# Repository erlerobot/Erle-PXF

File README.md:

Erle-PXF
===

Fork of the PXF board (http://github.com/diydrones/PXF) made by Erle Robotics.

This project is for developers, it will NOT be supported by the DIYDrones or Ardupilot suppoert forums for general users. This means we do not expect that this board will be plug and play, nor do we intend it to be.

Credit to Philip Rowse and Erle Robotics.

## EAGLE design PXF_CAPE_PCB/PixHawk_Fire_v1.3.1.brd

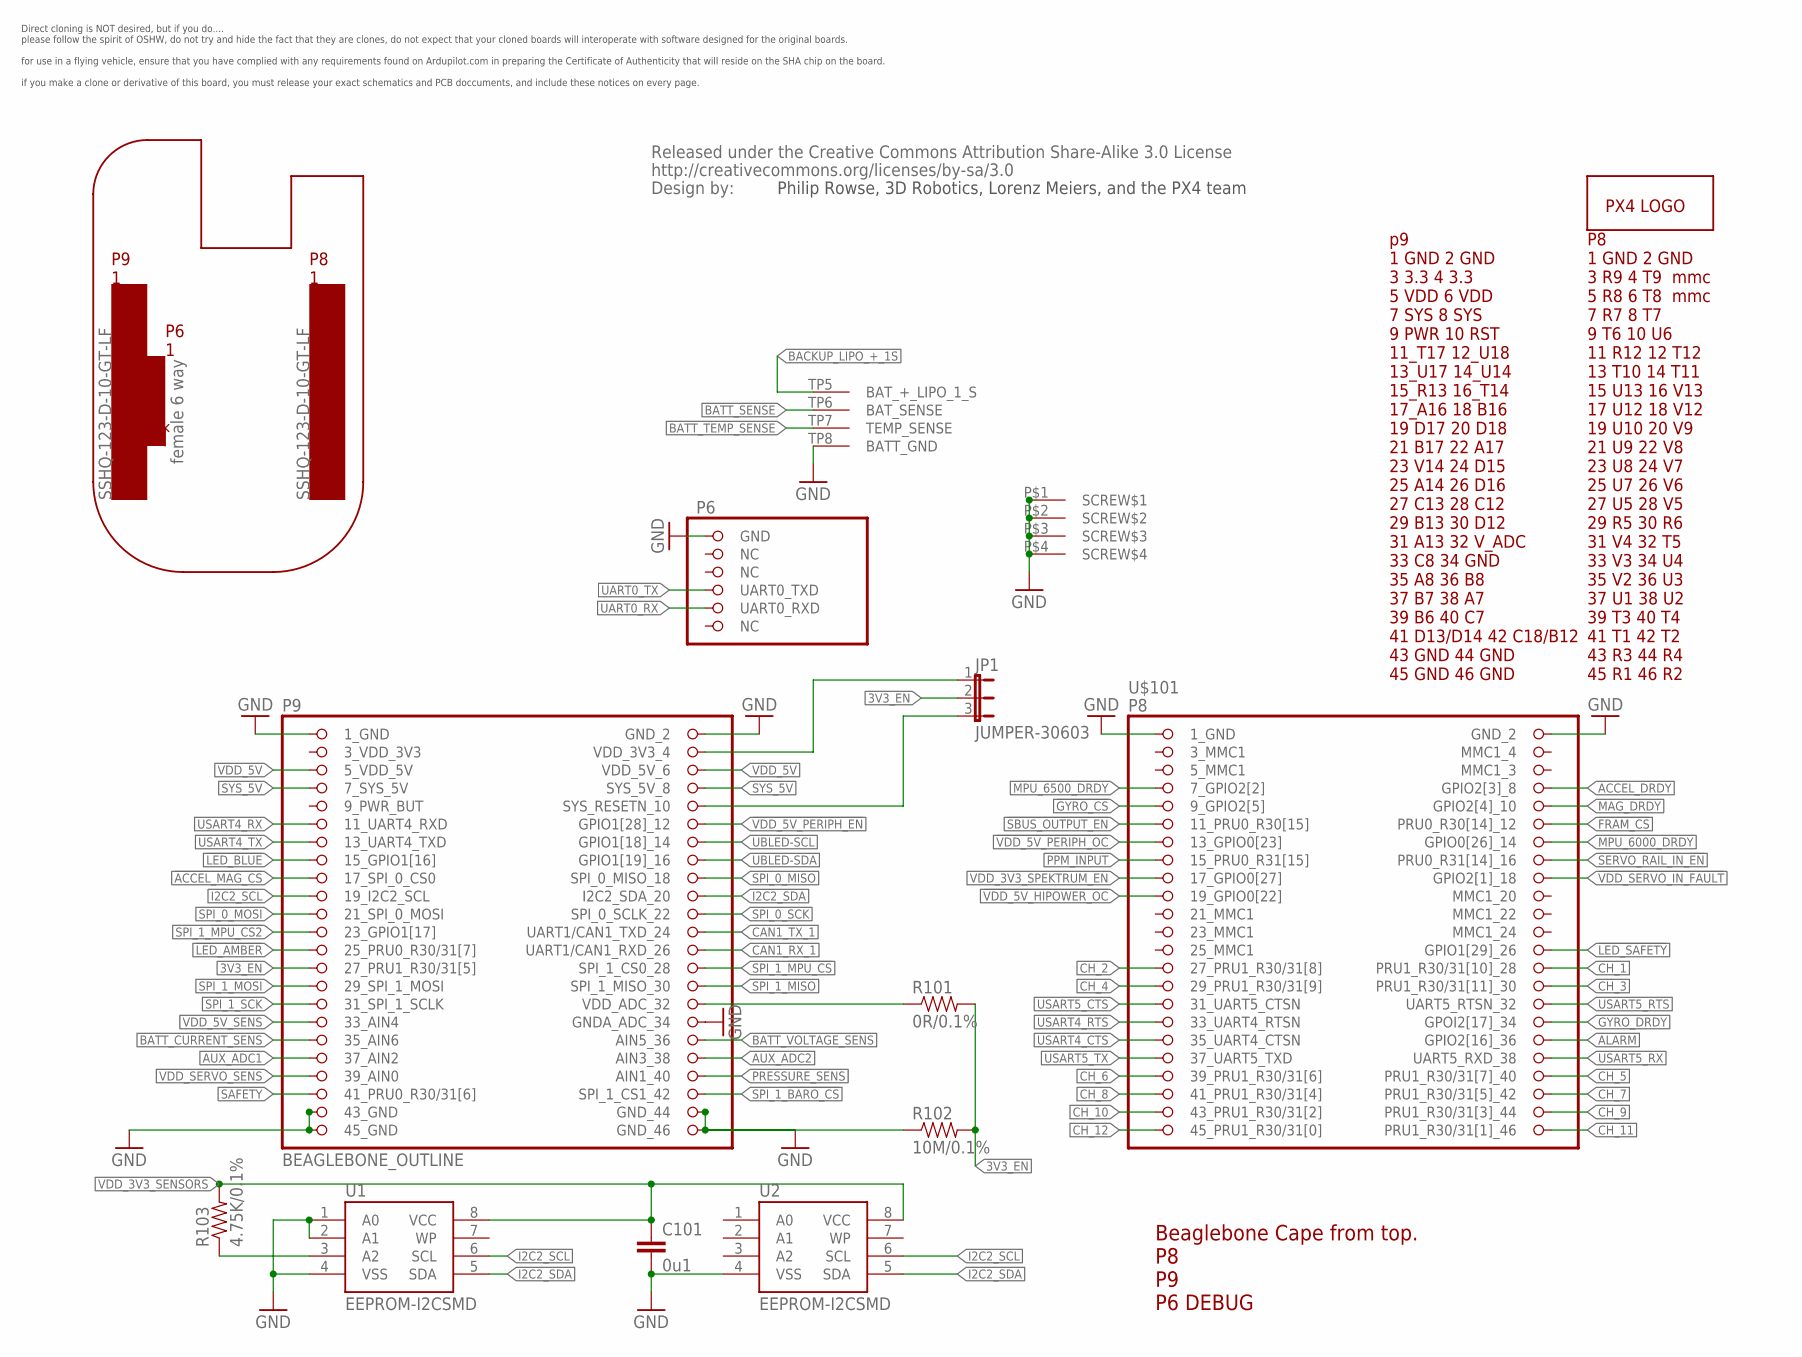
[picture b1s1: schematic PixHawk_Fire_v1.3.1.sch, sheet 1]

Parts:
C101: 0u1; 0402-CAP; PARTNO CC0402ZRY5V7BB104
JP1: JUMPER-30603; SJ_3_0603_PASTE1&2; PARTNO RC0603JR-070RL
R101: 0R/0.1%; 0402-RES; PARTNO RC0402FR-070RL
R102: 10M/0.1%; 0402-RES; PARTNO RC0402FR-0710ML
R103: 4.75K/0.1%; 0402-RES; PARTNO RC0402FR-074K75L
U1: EEPROM-I2CSMD; SO08; PARTNO AT24CS32-SSHM
U2: EEPROM-I2CSMD; SO08; PARTNO ATSHA204-SH-DA-TTR-ND
U$1: PX4-LOGO; PIXHAWK-FIRE-LOGO-30
U$6: CREATIVE_COMMONS
U$101: BEAGLEBONE_OUTLINE; BEAGLEBONE_SHIELD

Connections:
3V3_EN: JP1.2, R101.P$2 (2), R102.P$2 (2), U$101.73 (27_PRU1_R30/31[5]); also elsewhere on the board
3_VDD_3V3: U$101.49 (3_VDD_3V3)
!ACCEL_MAG_CS: U$101.63 (17_SPI_0_CS0); also elsewhere on the board
!FRAM_CS: U$101.12 (PRU0_R30[14]_12); also elsewhere on the board
!GYRO_CS: U$101.9 (9_GPIO2[5]); also elsewhere on the board
!LED_AMBER: U$101.71 (25_PRU0_R30/31[7]); also elsewhere on the board
!LED_BLUE: U$101.61 (15_GPIO1[16]); also elsewhere on the board
!LED_SAFETY: U$101.26 (GPIO1[29]_26); also elsewhere on the board
!SBUS_OUTPUT_EN: U$101.11 (11_PRU0_R30[15]); also elsewhere on the board
!VDD_5V_HIPOWER_OC: U$101.19 (19_GPIO0[22]); also elsewhere on the board
!VDD_5V_PERIPH_EN: U$101.58 (GPIO1[28]_12); also elsewhere on the board
!VDD_5V_PERIPH_OC: U$101.13 (13_GPIO0[23]); also elsewhere on the board
!VDD_SERVO_IN_FAULT: U$101.18 (GPIO2[1]_18); also elsewhere on the board
ACCEL_DRDY: U$101.8 (GPIO2[3]_8); also elsewhere on the board
ALARM: U$101.36 (GPIO2[16]_36); also elsewhere on the board
AUX_ADC1: U$101.83 (37_AIN2); also elsewhere on the board
AUX_ADC2: U$101.84 (AIN3_38); also elsewhere on the board
BACKUP_LIPO_+_1S: U$101.TP5 (BAT_+_LIPO_1_S); also elsewhere on the board
BATT_CURRENT_SENS: U$101.81 (35_AIN6); also elsewhere on the board
BATT_SENSE: U$101.TP6 (BAT_SENSE); also elsewhere on the board
BATT_TEMP_SENSE: U$101.TP7 (TEMP_SENSE); also elsewhere on the board
BATT_VOLTAGE_SENS: U$101.82 (AIN5_36); also elsewhere on the board
CH_1: U$101.28 (PRU1_R30/31[10]_28); also elsewhere on the board
CH_2: U$101.27 (27_PRU1_R30/31[8]); also elsewhere on the board
CH_3: U$101.30 (PRU1_R30/31[11]_30); also elsewhere on the board
CH_4: U$101.29 (29_PRU1_R30/31[9]); also elsewhere on the board
CH_5: U$101.40 (PRU1_R30/31[7]_40); also elsewhere on the board
CH_6: U$101.39 (39_PRU1_R30/31[6]); also elsewhere on the board
CH_7: U$101.42 (PRU1_R30/31[5]_42); also elsewhere on the board
CH_8: U$101.41 (41_PRU1_R30/31[4]); also elsewhere on the board
CH_9: U$101.44 (PRU1_R30/31[3]_44); also elsewhere on the board
CH_10: U$101.43 (43_PRU1_R30/31[2]); also elsewhere on the board
CH_11: U$101.46 (PRU1_R30/31[1]_46); also elsewhere on the board
CH_12: U$101.45 (45_PRU1_R30/31[0]); also elsewhere on the board
GND: C101.P$2 (2), R102.P$1 (1), U1.1 (A0), U1.2 (A1), U1.4 (VSS), U2.4 (VSS), U$101.1 (1_GND), U$101.2 (GND_2), U$101.47 (1_GND), U$101.48 (GND_2), U$101.80 (GNDA_ADC_34), U$101.89 (43_GND), U$101.90 (GND_44), U$101.91 (45_GND), U$101.92 (GND_46), U$101.93 (GND), U$101.P$1 (SCREW$1), U$101.P$2 (SCREW$2), U$101.P$3 (SCREW$3), U$101.P$4 (SCREW$4), U$101.TP8 (BATT_GND); also elsewhere on the board
GYRO_DRDY: U$101.34 (GPOI2[17]_34); also elsewhere on the board
I2C2_SCL: U1.6 (SCL), U2.6 (SCL), U$101.65 (19_I2C2_SCL); also elsewhere on the board
I2C2_SDA: U1.5 (SDA), U2.5 (SDA), U$101.66 (I2C2_SDA_20); also elsewhere on the board
MAG_DRDY: U$101.10 (GPIO2[4]_10); also elsewhere on the board
MPU_6000_DRDY: U$101.14 (GPIO0[26]_14); also elsewhere on the board
MPU_6500_DRDY: U$101.7 (7_GPIO2[2]); also elsewhere on the board
unnamed: R103.P$1 (1), U1.3 (A2)
unnamed: JP1.1, U$101.50 (VDD_3V3_4)
unnamed: JP1.3, U$101.56 (SYS_RESETN_10)
PPM_INPUT: U$101.15 (15_PRU0_R31[15]); also elsewhere on the board
PRESSURE_SENS: U$101.86 (AIN1_40); also elsewhere on the board
SAFETY: U$101.87 (41_PRU0_R30/31[6]); also elsewhere on the board
SERVO_RAIL_IN_!EN: U$101.16 (PRU0_R31[14]_16); also elsewhere on the board
SPI_0_MISO: U$101.64 (SPI_0_MISO_18); also elsewhere on the board
SPI_0_MOSI: U$101.67 (21_SPI_0_MOSI); also elsewhere on the board
SPI_0_SCK: U$101.68 (SPI_0_SCLK_22); also elsewhere on the board
SPI_1_!BARO_CS: U$101.88 (SPI_1_CS1_42); also elsewhere on the board
SPI_1_!MPU_CS: U$101.74 (SPI_1_CS0_28); also elsewhere on the board
SPI_1_!MPU_CS2: U$101.69 (23_GPIO1[17]); also elsewhere on the board
SPI_1_MISO: U$101.76 (SPI_1_MISO_30); also elsewhere on the board
SPI_1_MOSI: U$101.75 (29_SPI_1_MOSI); also elsewhere on the board
SPI_1_SCK: U$101.77 (31_SPI_1_SCLK); also elsewhere on the board
SYS_5V: U$101.53 (7_SYS_5V), U$101.54 (SYS_5V_8); also elsewhere on the board
UART0_RX: U$101.97 (UART0_RXD); also elsewhere on the board
UART0_TX: U$101.96 (UART0_TXD); also elsewhere on the board
UBLED-SCL: U$101.60 (GPIO1[18]_14); also elsewhere on the board
UBLED-SDA: U$101.62 (GPIO1[19]_16); also elsewhere on the board
USART4_CTS: U$101.35 (35_UART4_CTSN); also elsewhere on the board
USART4_RTS: U$101.33 (33_UART4_RTSN); also elsewhere on the board
USART4_RX: U$101.57 (11_UART4_RXD); also elsewhere on the board
USART4_TX: U$101.59 (13_UART4_TXD); also elsewhere on the board
USART5_CTS: U$101.31 (31_UART5_CTSN); also elsewhere on the board
USART5_RTS: U$101.32 (UART5_RTSN_32); also elsewhere on the board
USART5_RX: U$101.38 (UART5_RXD_38); also elsewhere on the board
USART5_TX: U$101.37 (37_UART5_TXD); also elsewhere on the board
VDD_3V3_SENSORS: C101.P$1 (1), R103.P$2 (2), U1.8 (VCC), U2.8 (VCC); also elsewhere on the board
VDD_3V3_SPEKTRUM_EN: U$101.17 (17_GPIO0[27]); also elsewhere on the board
VDD_5V: U$101.51 (5_VDD_5V), U$101.52 (VDD_5V_6); also elsewhere on the board
VDD_5V_SENS: U$101.79 (33_AIN4); also elsewhere on the board
VDD_ADC: R101.P$1 (1), U$101.78 (VDD_ADC_32)
VDD_SERVO_SENS: U$101.85 (39_AIN0); also elsewhere on the board

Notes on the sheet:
Beaglebone Cape from top. P8 P9 P6 DEBUG
Philip Rowse, 3D Robotics, Lorenz Meiers, and the PX4 team
Direct cloning is NOT desired, but if you do.... please follow the spirit of OSHW, do not try and hide the fact that they are clones, do not expect that your cloned boards will interoperate with software designed for the original boards. for use in a flying vehicle, ensure that you have complied wi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

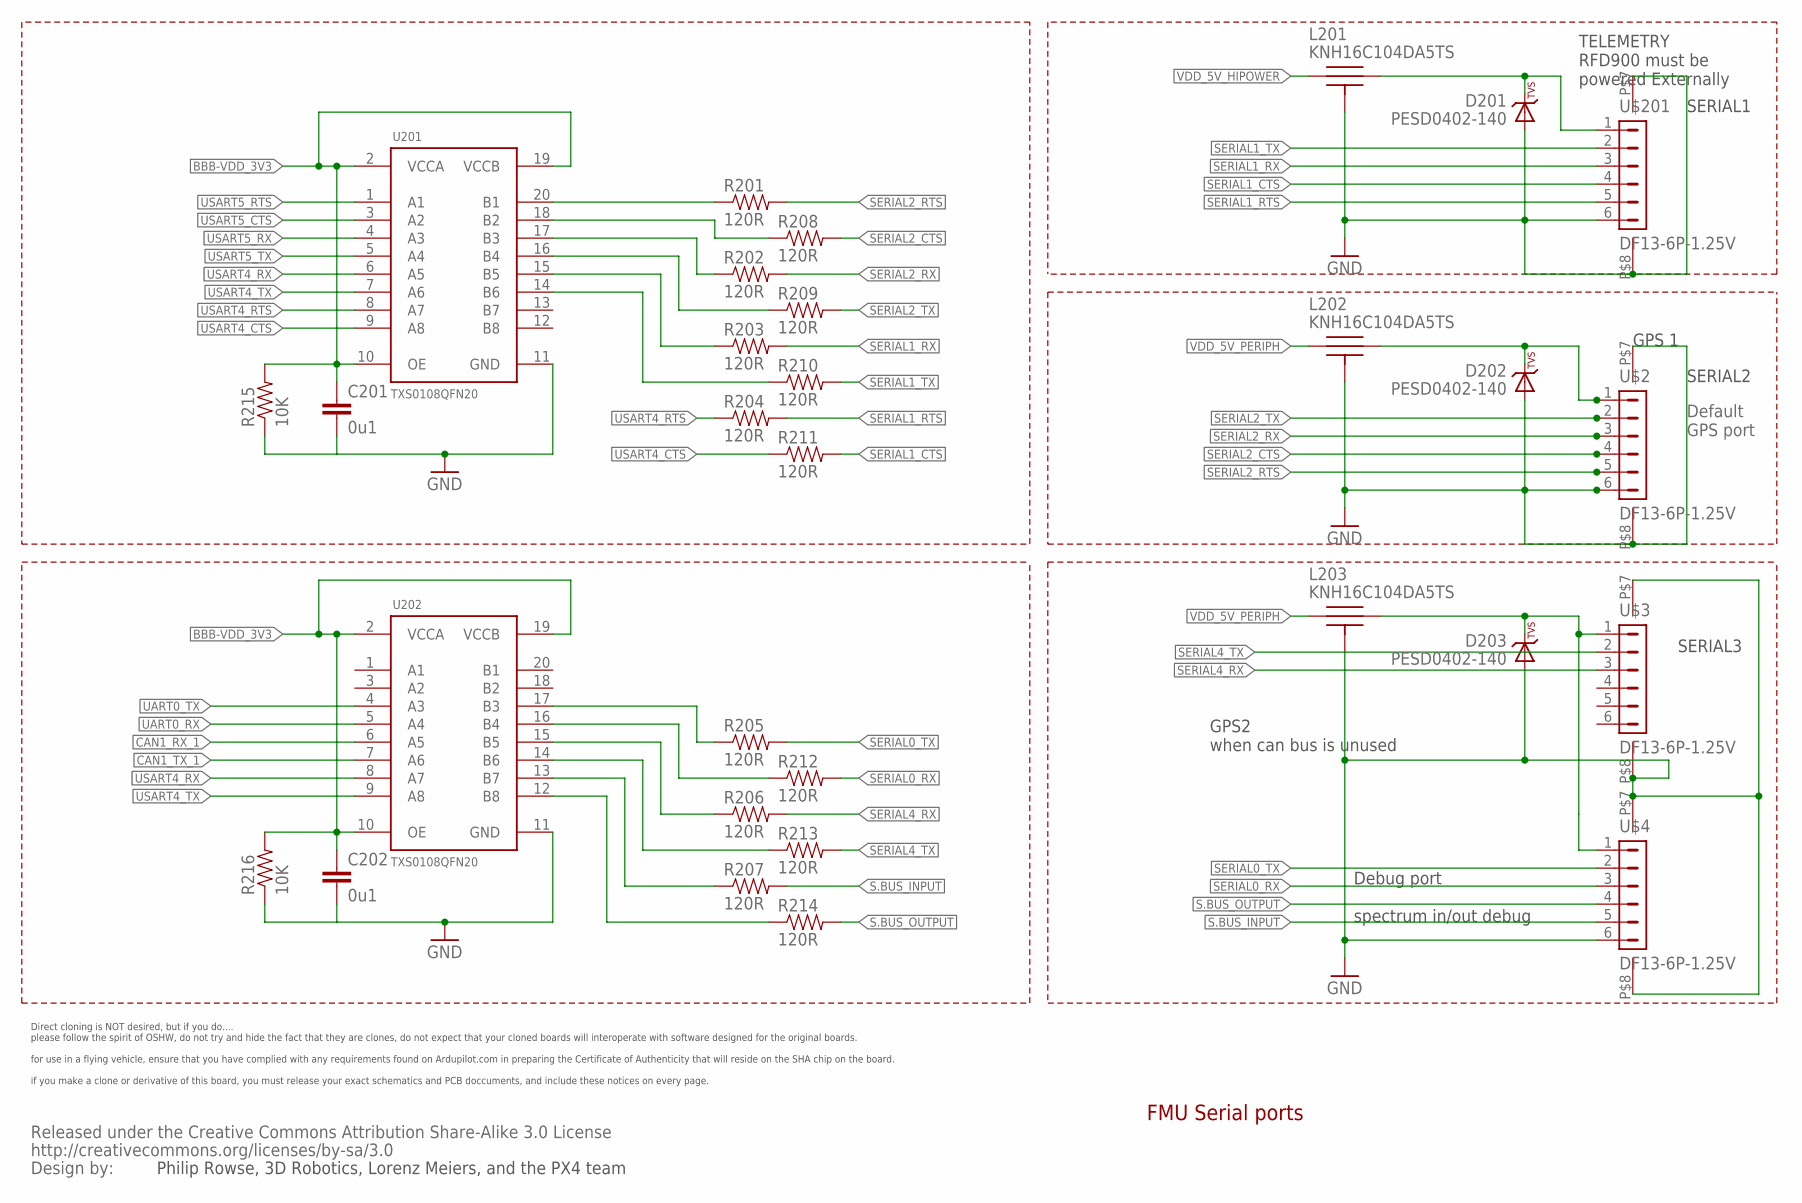
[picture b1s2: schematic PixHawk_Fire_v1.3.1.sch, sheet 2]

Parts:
C201, C202: 0u1; 0402-CAP; PARTNO CC0402ZRY5V7BB104
D201, D202, D203: PESD0402-140; 0402-TVS; PARTNO PESD0402-140
L201, L202, L203: KNH16C104DA5TS; KYOCERA-KNH16-DA; PARTNO KNH16C104DA5TS
R201, R202, R203, R204, R205, R206, R207, R208, R209, R210, R211, R212, R213, R214: 120R; 0402-RES; PARTNO RC0402FR-07120RL
R215, R216: 10K; 0402-RES; PARTNO ERA-2AEB103X
U201, U202: TXS0108QFN20; QFN20-RGY; PARTNO TXS0108ERGYR
U$2, U$3, U$4, U$201: DF13-6P-1.25V; DF13C-6P-1.25V; PARTNO DF13C-6P-1.25V(20)
U$5: CREATIVE_COMMONS

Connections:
BBB-VDD_3V3: C201.P$1 (1), C202.P$1 (1), R215.P$2 (2), R216.P$2 (2), U201.2 (VCCA), U201.10 (OE), U201.19 (VCCB), U202.2 (VCCA), U202.10 (OE), U202.19 (VCCB); also elsewhere on the board
CAN1_RX_1: U202.6 (A5); also elsewhere on the board
CAN1_TX_1: U202.7 (A6); also elsewhere on the board
GND: C201.P$2 (2), C202.P$2 (2), D201.A, D202.A, D203.A, L201.P$3, L201.P$4, L201.P$5, L202.P$3, L202.P$4, L202.P$5, L203.P$3, L203.P$4, L203.P$5, R215.P$1 (1), R216.P$1 (1), U201.11 (GND), U202.11 (GND), U$2.6, U$2.P$7, U$2.P$8, U$3.P$7, U$3.P$8, U$4.6, U$4.P$7, U$4.P$8, U$201.6, U$201.P$7, U$201.P$8; also elsewhere on the board
unnamed: D201.C, L201.P$2, U$201.1
unnamed: R205.P$1 (1), U202.17 (B3)
unnamed: R212.P$1 (1), U202.16 (B4)
unnamed: R208.P$1 (1), U201.18 (B2)
unnamed: R201.P$1 (1), U201.20 (B1)
unnamed: R202.P$1 (1), U201.17 (B3)
unnamed: R209.P$1 (1), U201.16 (B4)
unnamed: R203.P$1 (1), U201.15 (B5)
unnamed: R210.P$1 (1), U201.14 (B6)
unnamed: R207.P$1 (1), U202.13 (B7)
unnamed: R214.P$1 (1), U202.12 (B8)
unnamed: R206.P$1 (1), U202.15 (B5)
unnamed: R213.P$1 (1), U202.14 (B6)
unnamed: D203.C, L203.P$2, U$3.1, U$4.1
unnamed: D202.C, L202.P$2, U$2.1
S.BUS_INPUT: R207.P$2 (2), U$4.5; also elsewhere on the board
S.BUS_OUTPUT: R214.P$2 (2), U$4.4; also elsewhere on the board
SERIAL0_RX: R212.P$2 (2), U$4.3
SERIAL0_TX: R205.P$2 (2), U$4.2
SERIAL1_CTS: R211.P$2 (2), U$201.4
SERIAL1_RTS: R204.P$2 (2), U$201.5
SERIAL1_RX: R203.P$2 (2), U$201.3; also elsewhere on the board
SERIAL1_TX: R210.P$2 (2), U$201.2; also elsewhere on the board
SERIAL2_CTS: R208.P$2 (2), U$2.4
SERIAL2_RTS: R201.P$2 (2), U$2.5
SERIAL2_RX: R202.P$2 (2), U$2.3; also elsewhere on the board
SERIAL2_TX: R209.P$2 (2), U$2.2; also elsewhere on the board
SERIAL4_RX: R206.P$2 (2), U$3.3; also elsewhere on the board
SERIAL4_TX: R213.P$2 (2), U$3.2; also elsewhere on the board
UART0_RX: U202.5 (A4); also elsewhere on the board
UART0_TX: U202.4 (A3); also elsewhere on the board
USART4_CTS: R211.P$1 (1), U201.9 (A8); also elsewhere on the board
USART4_RTS: R204.P$1 (1), U201.8 (A7); also elsewhere on the board
USART4_RX: U201.6 (A5), U202.8 (A7); also elsewhere on the board
USART4_TX: U201.7 (A6), U202.9 (A8); also elsewhere on the board
USART5_CTS: U201.3 (A2); also elsewhere on the board
USART5_RTS: U201.1 (A1); also elsewhere on the board
USART5_RX: U201.4 (A3); also elsewhere on the board
USART5_TX: U201.5 (A4); also elsewhere on the board
VDD_5V_HIPOWER: L201.P$1; also elsewhere on the board
VDD_5V_PERIPH: L202.P$1, L203.P$1; also elsewhere on the board

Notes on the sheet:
FMU Serial ports
SERIAL2
SERIAL1
SERIAL3
Default GPS port
TELEMETRY RFD900 must be powered Externally
GPS 1
Debug port spectrum in/out debug
GPS2 when can bus is unused
Philip Rowse, 3D Robotics, Lorenz Meiers, and the PX4 team
Direct cloning is NOT desired, but if you do.... please follow the spirit of OSHW, do not try and hide the fact that they are clones, do not expect that your cloned boards will interoperate with software designed for the original boards. for use in a flying vehicle, ensure that you have complied wi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

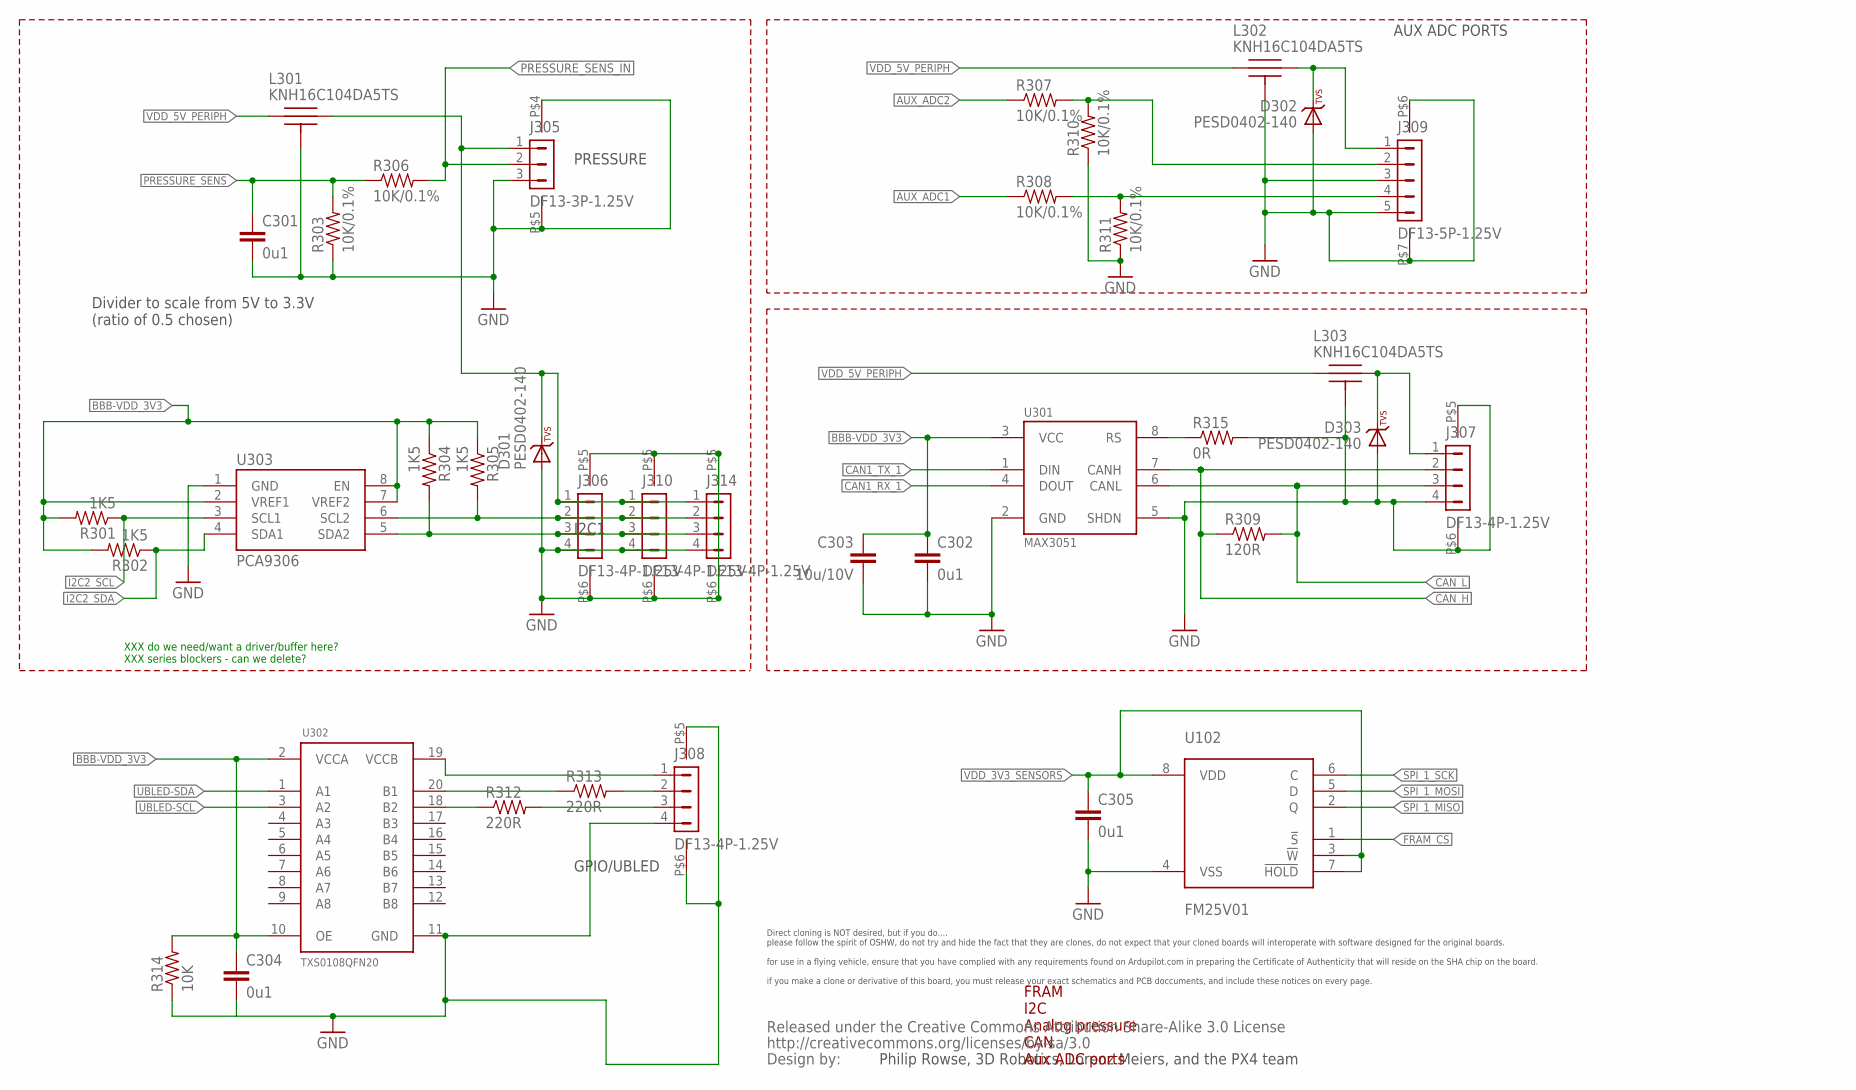
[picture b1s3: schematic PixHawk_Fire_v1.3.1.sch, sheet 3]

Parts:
C301, C302, C304, C305: 0u1; 0402-CAP; PARTNO CC0402ZRY5V7BB104
C303: 10u/10V; 0805-CAP; PARTNO CC0805ZKY5V6BB106
D301, D302, D303: PESD0402-140; 0402-TVS; PARTNO PESD0402-140
J305: DF13-3P-1.25V; DF13C-3P-1.25V; PARTNO DF13C-3P-1.25V(20)
J306, J307, J308, J310, J314: DF13-4P-1.25V; DF13C-4P-1.25V; PARTNO DF13C-4P-1.25V(20)
J309: DF13-5P-1.25V; DF13C-5P-1.25V; PARTNO DF13C-5P-1.25V(20)
L301, L302, L303: KNH16C104DA5TS; KYOCERA-KNH16-DA; PARTNO KNH16C104DA5TS
R301, R302, R304, R305: 1K5; 0402-RES; PARTNO RC0402FR-071K5L
R303, R306, R307, R308, R310, R311: 10K/0.1%; 0402-RES; PARTNO ERA-2AEB103X
R309: 120R; 0402-RES; PARTNO RC0402FR-07120RL
R312, R313: 220R; 0402-RES; PARTNO RC0402FR-07220RL
R314: 10K; 0402-RES; PARTNO ERA-2AEB103X
R315: 0R; 0402-RES; PARTNO RC0402FR-070RL
U102: FM25V01; SO08; PARTNO FM25V01-G
U301: MAX3051; SOT23-8; PARTNO MAX3051EKA
U302: TXS0108QFN20; QFN20-RGY; PARTNO TXS0108ERGYR
U303: PCA9306; PARTNO PCA9306DQER
U$7: CREATIVE_COMMONS

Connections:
!FRAM_CS: U102.1 (!S); also elsewhere on the board
AUX_ADC1: R308.P$1 (1); also elsewhere on the board
AUX_ADC2: R307.P$1 (1); also elsewhere on the board
BBB-VDD_3V3: C302.P$1 (1), C303.P$1 (1), C304.P$1 (1), R301.P$2 (2), R302.P$2 (2), R304.P$1 (1), R305.P$1 (1), R314.P$2 (2), U301.3 (VCC), U302.2 (VCCA), U302.10 (OE), U303.2 (VREF1), U303.7 (VREF2), U303.8 (EN); also elsewhere on the board
CAN1_RX_1: U301.4 (DOUT); also elsewhere on the board
CAN1_TX_1: U301.1 (DIN); also elsewhere on the board
CAN_H: J307.2, R309.P$1 (1), U301.7 (CANH); also elsewhere on the board
CAN_L: J307.3, R309.P$2 (2), U301.6 (CANL); also elsewhere on the board
FMU_AUX_ADC1_PROT: J309.4, R308.P$2 (2), R311.P$2 (2)
FMU_AUX_ADC2_PROT: J309.2, R307.P$2 (2), R310.P$2 (2)
GND: C301.P$2 (2), C302.P$2 (2), C303.P$2 (2), C304.P$2 (2), C305.P$2 (2), D301.A, D302.A, D303.A, J305.3, J305.P$4, J305.P$5, J306.4, J306.P$5, J306.P$6, J307.4, J307.P$5, J307.P$6, J308.4, J308.P$5, J308.P$6, J309.3, J309.5, J309.P$6, J309.P$7, J310.4, J310.P$5, J310.P$6, J314.4, J314.P$5, J314.P$6, L301.P$3, L301.P$4, L301.P$5, L302.P$3, L302.P$4, L302.P$5, L303.P$3, L303.P$4, L303.P$5, R303.P$1 (1), R310.P$1 (1), R311.P$1 (1), R314.P$1 (1), R315.P$2 (2), U102.4 (VSS), U301.2 (GND), U301.5 (SHDN), U302.11 (GND), U303.1 (GND); also elsewhere on the board
I2C2_SCL: R301.P$1 (1), U303.3 (SCL1); also elsewhere on the board
I2C2_SDA: R302.P$1 (1), U303.4 (SDA1); also elsewhere on the board
unnamed: R313.P$1 (1), U302.20 (B1)
unnamed: J306.2, J310.2, J314.2, R305.P$2 (2), U303.6 (SCL2)
unnamed: J306.3, J310.3, J314.3, R304.P$2 (2), U303.5 (SDA2)
unnamed: R312.P$1 (1), U302.18 (B2)
unnamed: D301.C, J305.1, J306.1, J310.1, J314.1, L301.P$2
unnamed: J308.3, R312.P$2 (2)
unnamed: J308.2, R313.P$2 (2)
unnamed: J308.1, U302.19 (VCCB)
unnamed: D303.C, J307.1, L303.P$2
unnamed: R315.P$1 (1), U301.8 (RS)
unnamed: D302.C, J309.1, L302.P$2
PRESSURE_SENS: C301.P$1 (1), R303.P$2 (2), R306.P$1 (1); also elsewhere on the board
PRESSURE_SENS_IN: J305.2, R306.P$2 (2); also elsewhere on the board
SPI_1_MISO: U102.2 (Q); also elsewhere on the board
SPI_1_MOSI: U102.5 (D); also elsewhere on the board
SPI_1_SCK: U102.6 (C); also elsewhere on the board
UBLED-SCL: U302.3 (A2); also elsewhere on the board
UBLED-SDA: U302.1 (A1); also elsewhere on the board
VDD_3V3_SENSORS: C305.P$1 (1), U102.3 (!W), U102.7 (!HOLD), U102.8 (VDD); also elsewhere on the board
VDD_5V_PERIPH: L301.P$1, L302.P$1, L303.P$1; also elsewhere on the board

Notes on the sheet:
PRESSURE
XXX do we need/want a driver/buffer here? XXX series blockers - can we delete?
I2C1
AUX ADC PORTS
FRAM I2C Analog pressure CAN Aux ADC ports
Divider to scale from 5V to 3.3V (ratio of 0.5 chosen)
GPIO/UBLED
Philip Rowse, 3D Robotics, Lorenz Meiers, and the PX4 team
Direct cloning is NOT desired, but if you do.... please follow the spirit of OSHW, do not try and hide the fact that they are clones, do not expect that your cloned boards will interoperate with software designed for the original boards. for use in a flying vehicle, ensure that you have complied wi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

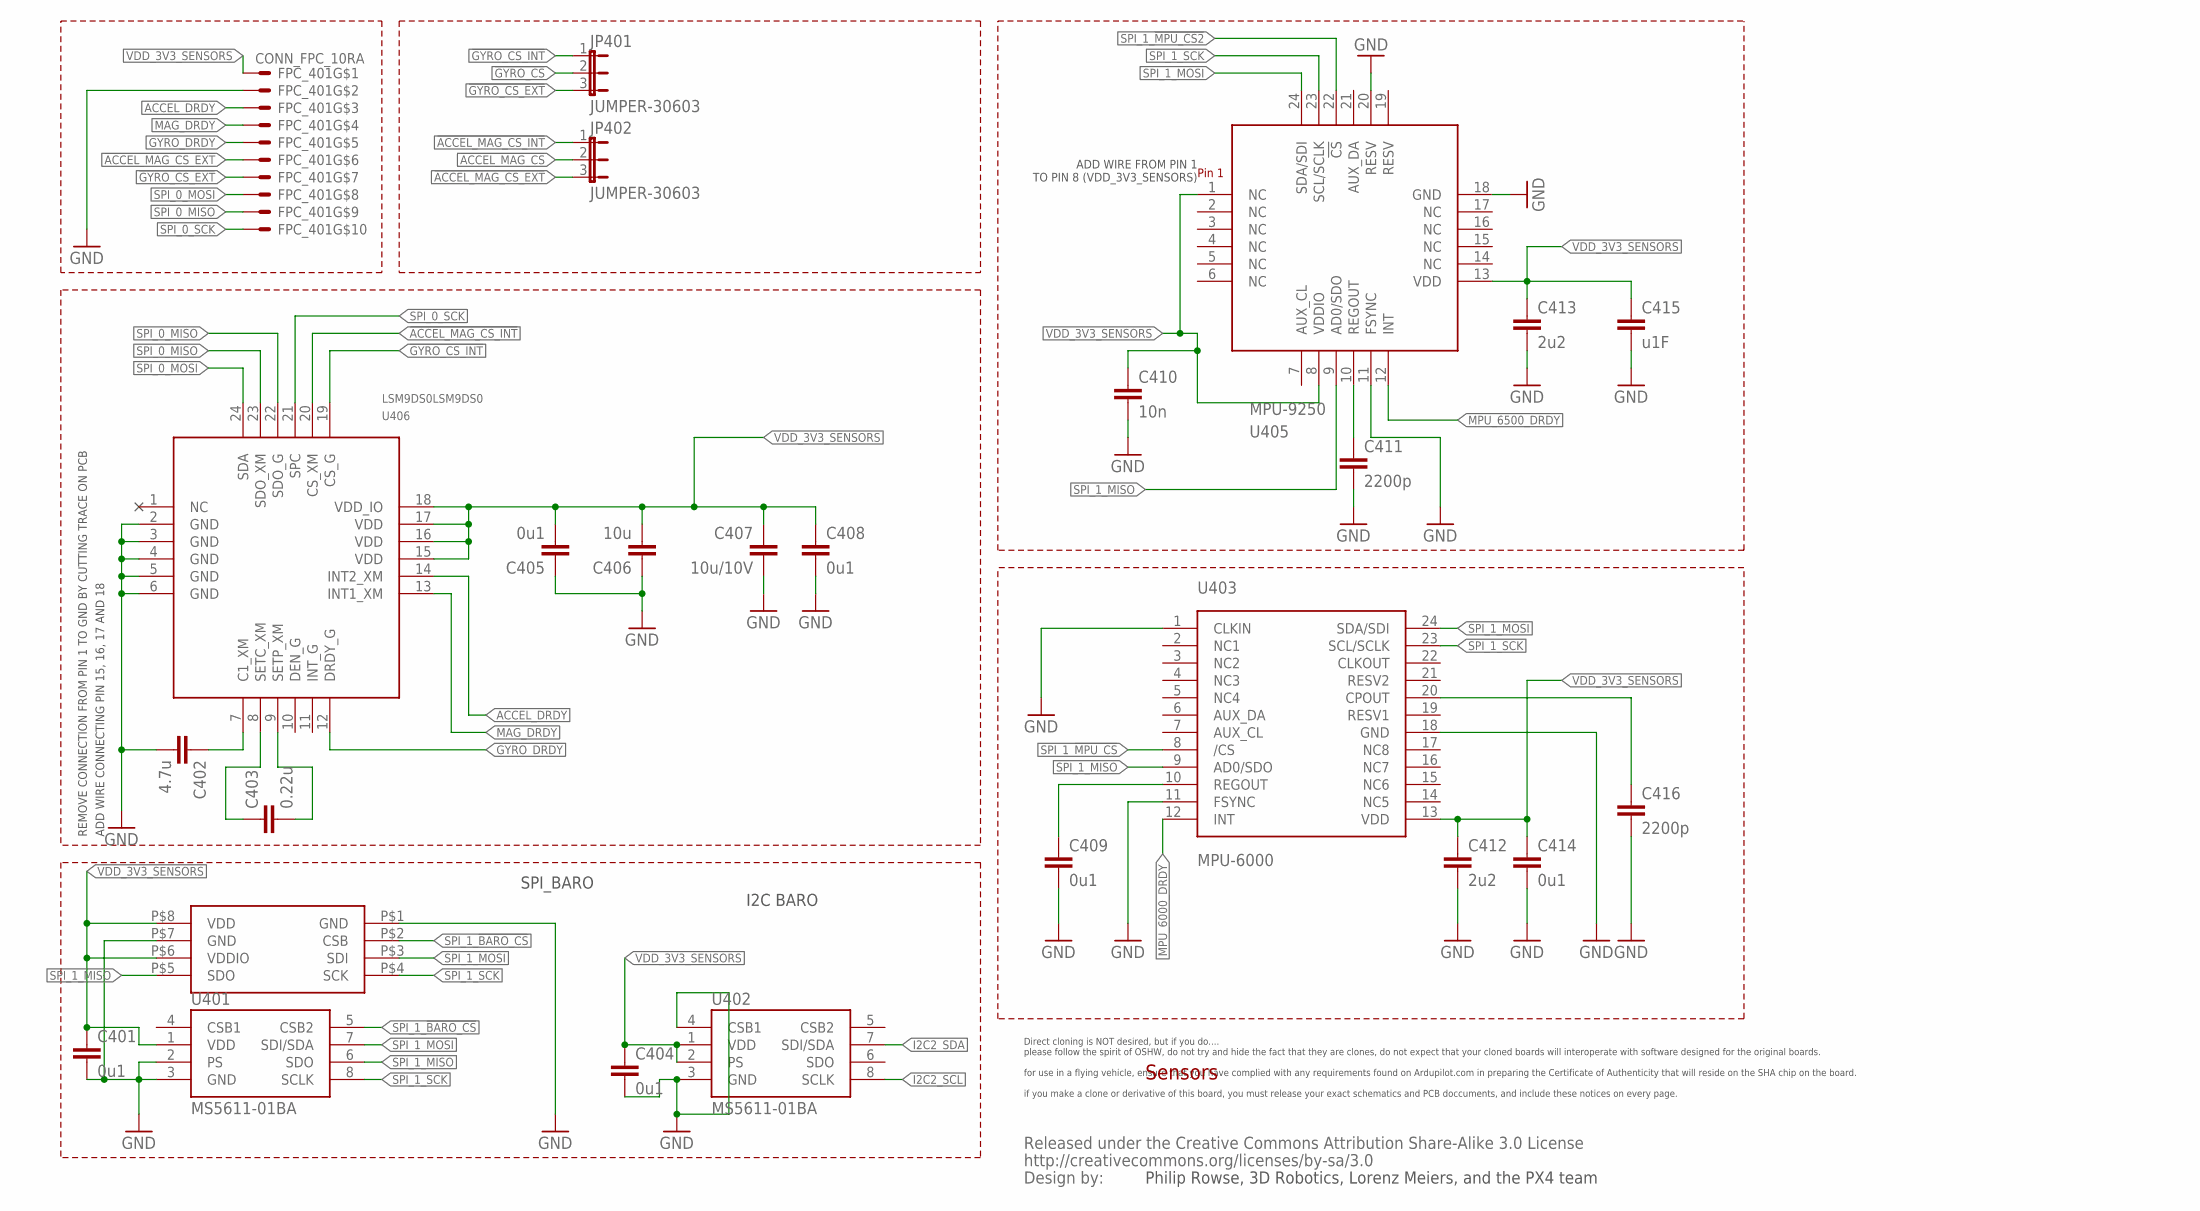
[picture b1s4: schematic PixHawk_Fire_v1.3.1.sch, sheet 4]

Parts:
C401, C404, C408: 0u1; 0402-CAP; PARTNO CC0402ZRY5V7BB104
C402: 4.7u; 0603-CAP; PARTNO C1608X7S1A475K080AC
C403: 0.22u; 0603-CAP; PARTNO CL10B224JP8NNNC
C405: 0u1; 0603-CAP; PARTNO CL10B104JO8NNNC
C406: 10u; 0603-CAP; PARTNO C1608X7S0J106M080AC
C407: 10u/10V; 0805-CAP; PARTNO CC0805ZKY5V6BB106
C409: 0u1; 0603-CAP; PARTNO C0603C104K4RACTU
C410: 10n; 0603-CAP; PARTNO C0603C103J5RAC7411
C411, C416: 2200p; 0603-CAP; PARTNO C0603C222J5RACTU
C412: 2u2; 0603-CAP; PARTNO CGA3E1X7R0J225K080AC
C413: 2u2; 0603-CAP
C414: 0u1; 0402-CAP; PARTNO C0603C104K4RACTU
C415: u1F; 0402-CAP; PARTNO CC0402ZRY5V7BB104
FPC_401: CONN_FPC_10RA; 51281-1094; PARTNO 0512811094
JP401, JP402: JUMPER-30603; SJ_3_0603_PASTE1&2; PARTNO RC0603JR-070RL
U401, U402: MS5611-01BA; PARTNO MS5611-01BA
U403: MPU-6000; QFN-24; PARTNO MPU-6000
U405: MPU-9250; MPU-6500; PARTNO MPU-9250
U406: LSM9DS0LSM9DS0; LSM9DS0; PARTNO LSM9DS0TR
U407: BMP280_PRELIM; PARTNO *
U$8: CREATIVE_COMMONS

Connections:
!ACCEL_MAG_CS: JP402.2; also elsewhere on the board
!ACCEL_MAG_CS_EXT: FPC_401.6, JP402.3
!ACCEL_MAG_CS_INT: JP402.1, U406.20 (CS_XM)
!GYRO_CS: JP401.2; also elsewhere on the board
!GYRO_CS_EXT: FPC_401.7, JP401.3
!GYRO_CS_INT: JP401.1, U406.19 (CS_G)
ACCEL_DRDY: FPC_401.3, U406.14 (INT2_XM); also elsewhere on the board
GND: C401.P$2 (2), C402.P$2 (2), C404.P$2 (2), C405.P$1 (1), C406.P$1 (1), C407.P$2 (2), C408.P$2 (2), C409.P$2 (2), C410.P$2 (2), C411.P$2 (2), C412.P$2 (2), C413.P$2 (2), C414.P$2 (2), C415.P$2 (2), C416.P$2 (2), FPC_401.2, U401.2 (PS), U401.3 (GND), U402.3 (GND), U402.4 (CSB1), U403.1 (CLKIN), U403.11 (FSYNC), U403.18 (GND), U405.11 (FSYNC), U405.18 (GND), U405.20 (RESV), U406.2 (GND), U406.3 (GND), U406.4 (GND), U406.5 (GND), U406.6 (GND), U407.P$1 (GND), U407.P$7 (GND); also elsewhere on the board
GYRO_DRDY: FPC_401.5, U406.12 (DRDY_G); also elsewhere on the board
I2C2_SCL: U402.8 (SCLK); also elsewhere on the board
I2C2_SDA: U402.7 (SDI/SDA); also elsewhere on the board
MAG_DRDY: FPC_401.4, U406.13 (INT1_XM); also elsewhere on the board
MPU_6000_DRDY: U403.12 (INT); also elsewhere on the board
MPU_6500_DRDY: U405.12 (INT); also elsewhere on the board
unnamed: C402.P$1 (1), U406.7 (C1_XM)
unnamed: C403.P$2 (2), U406.9 (SETP_XM)
unnamed: C411.P$1 (1), U405.10 (REGOUT)
unnamed: C403.P$1 (1), U406.8 (SETC_XM)
unnamed: C409.P$1 (1), U403.10 (REGOUT)
unnamed: C416.P$1 (1), U403.20 (CPOUT)
SPI_0_MISO: FPC_401.9, U406.22 (SDO_G), U406.23 (SDO_XM); also elsewhere on the board
SPI_0_MOSI: FPC_401.8, U406.24 (SDA); also elsewhere on the board
SPI_0_SCK: FPC_401.10, U406.21 (SPC); also elsewhere on the board
SPI_1_!BARO_CS: U401.5 (CSB2), U407.P$2 (CSB); also elsewhere on the board
SPI_1_!MPU_CS: U403.8 (/CS); also elsewhere on the board
SPI_1_!MPU_CS2: U405.22 (!CS); also elsewhere on the board
SPI_1_MISO: U401.6 (SDO), U403.9 (AD0/SDO), U405.9 (AD0/SDO), U407.P$5 (SDO); also elsewhere on the board
SPI_1_MOSI: U401.7 (SDI/SDA), U403.24 (SDA/SDI), U405.24 (SDA/SDI), U407.P$3 (SDI); also elsewhere on the board
SPI_1_SCK: U401.8 (SCLK), U403.23 (SCL/SCLK), U405.23 (SCL/SCLK), U407.P$4 (SCK); also elsewhere on the board
VDD_3V3_SENSORS: C401.P$1 (1), C404.P$1 (1), C405.P$2 (2), C406.P$2 (2), C407.P$1 (1), C408.P$1 (1), C410.P$1 (1), C412.P$1 (1), C413.P$1 (1), C414.P$1 (1), C415.P$1 (1), FPC_401.1, U401.1 (VDD), U402.1 (VDD), U402.2 (PS), U403.13 (VDD), U405.1 (NC), U405.8 (VDDIO), U405.13 (VDD), U406.15 (VDD), U406.16 (VDD), U406.17 (VDD), U406.18 (VDD_IO), U407.P$6 (VDDIO), U407.P$8 (VDD); also elsewhere on the board

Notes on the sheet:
Sensors
I2C BARO
SPI_BARO
REMOVE CONNECTION FROM PIN 1 TO GND BY CUTTING TRACE ON PCB
ADD WIRE FROM PIN 1 TO PIN 8 (VDD_3V3_SENSORS)
ADD WIRE CONNECTING PIN 15, 16, 17 AND 18
Philip Rowse, 3D Robotics, Lorenz Meiers, and the PX4 team
Direct cloning is NOT desired, but if you do.... please follow the spirit of OSHW, do not try and hide the fact that they are clones, do not expect that your cloned boards will interoperate with software designed for the original boards. for use in a flying vehicle, ensure that you have complied wi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

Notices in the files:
PXF_CAPE_PCB/PixHawk_Fire_v1.3.1.brd:
(c)2014  Erle,PR,LM,3DR,AT,BN,AP
parts and their libraries:
SparkFun: Released under the Creative Commons Attribution Share-Alike 3.0 License
SparkFun: http://creativecommons.org/licenses/by-sa/3.0
